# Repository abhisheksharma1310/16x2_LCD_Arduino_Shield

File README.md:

# 16x2_LCD_Arduino_Shield
This is a PCB Design for an Arduino shield that can be stacked on top of the Arduino Board. It contains a 16x2 LCD Display which is used to display Sensor data or desired message on the 16x2 LCD Display. It also has one NRF24 Wireless Transmitter to send data wirelessly to display on 16x2 LCD.

Top view

Bottom view

Schematic

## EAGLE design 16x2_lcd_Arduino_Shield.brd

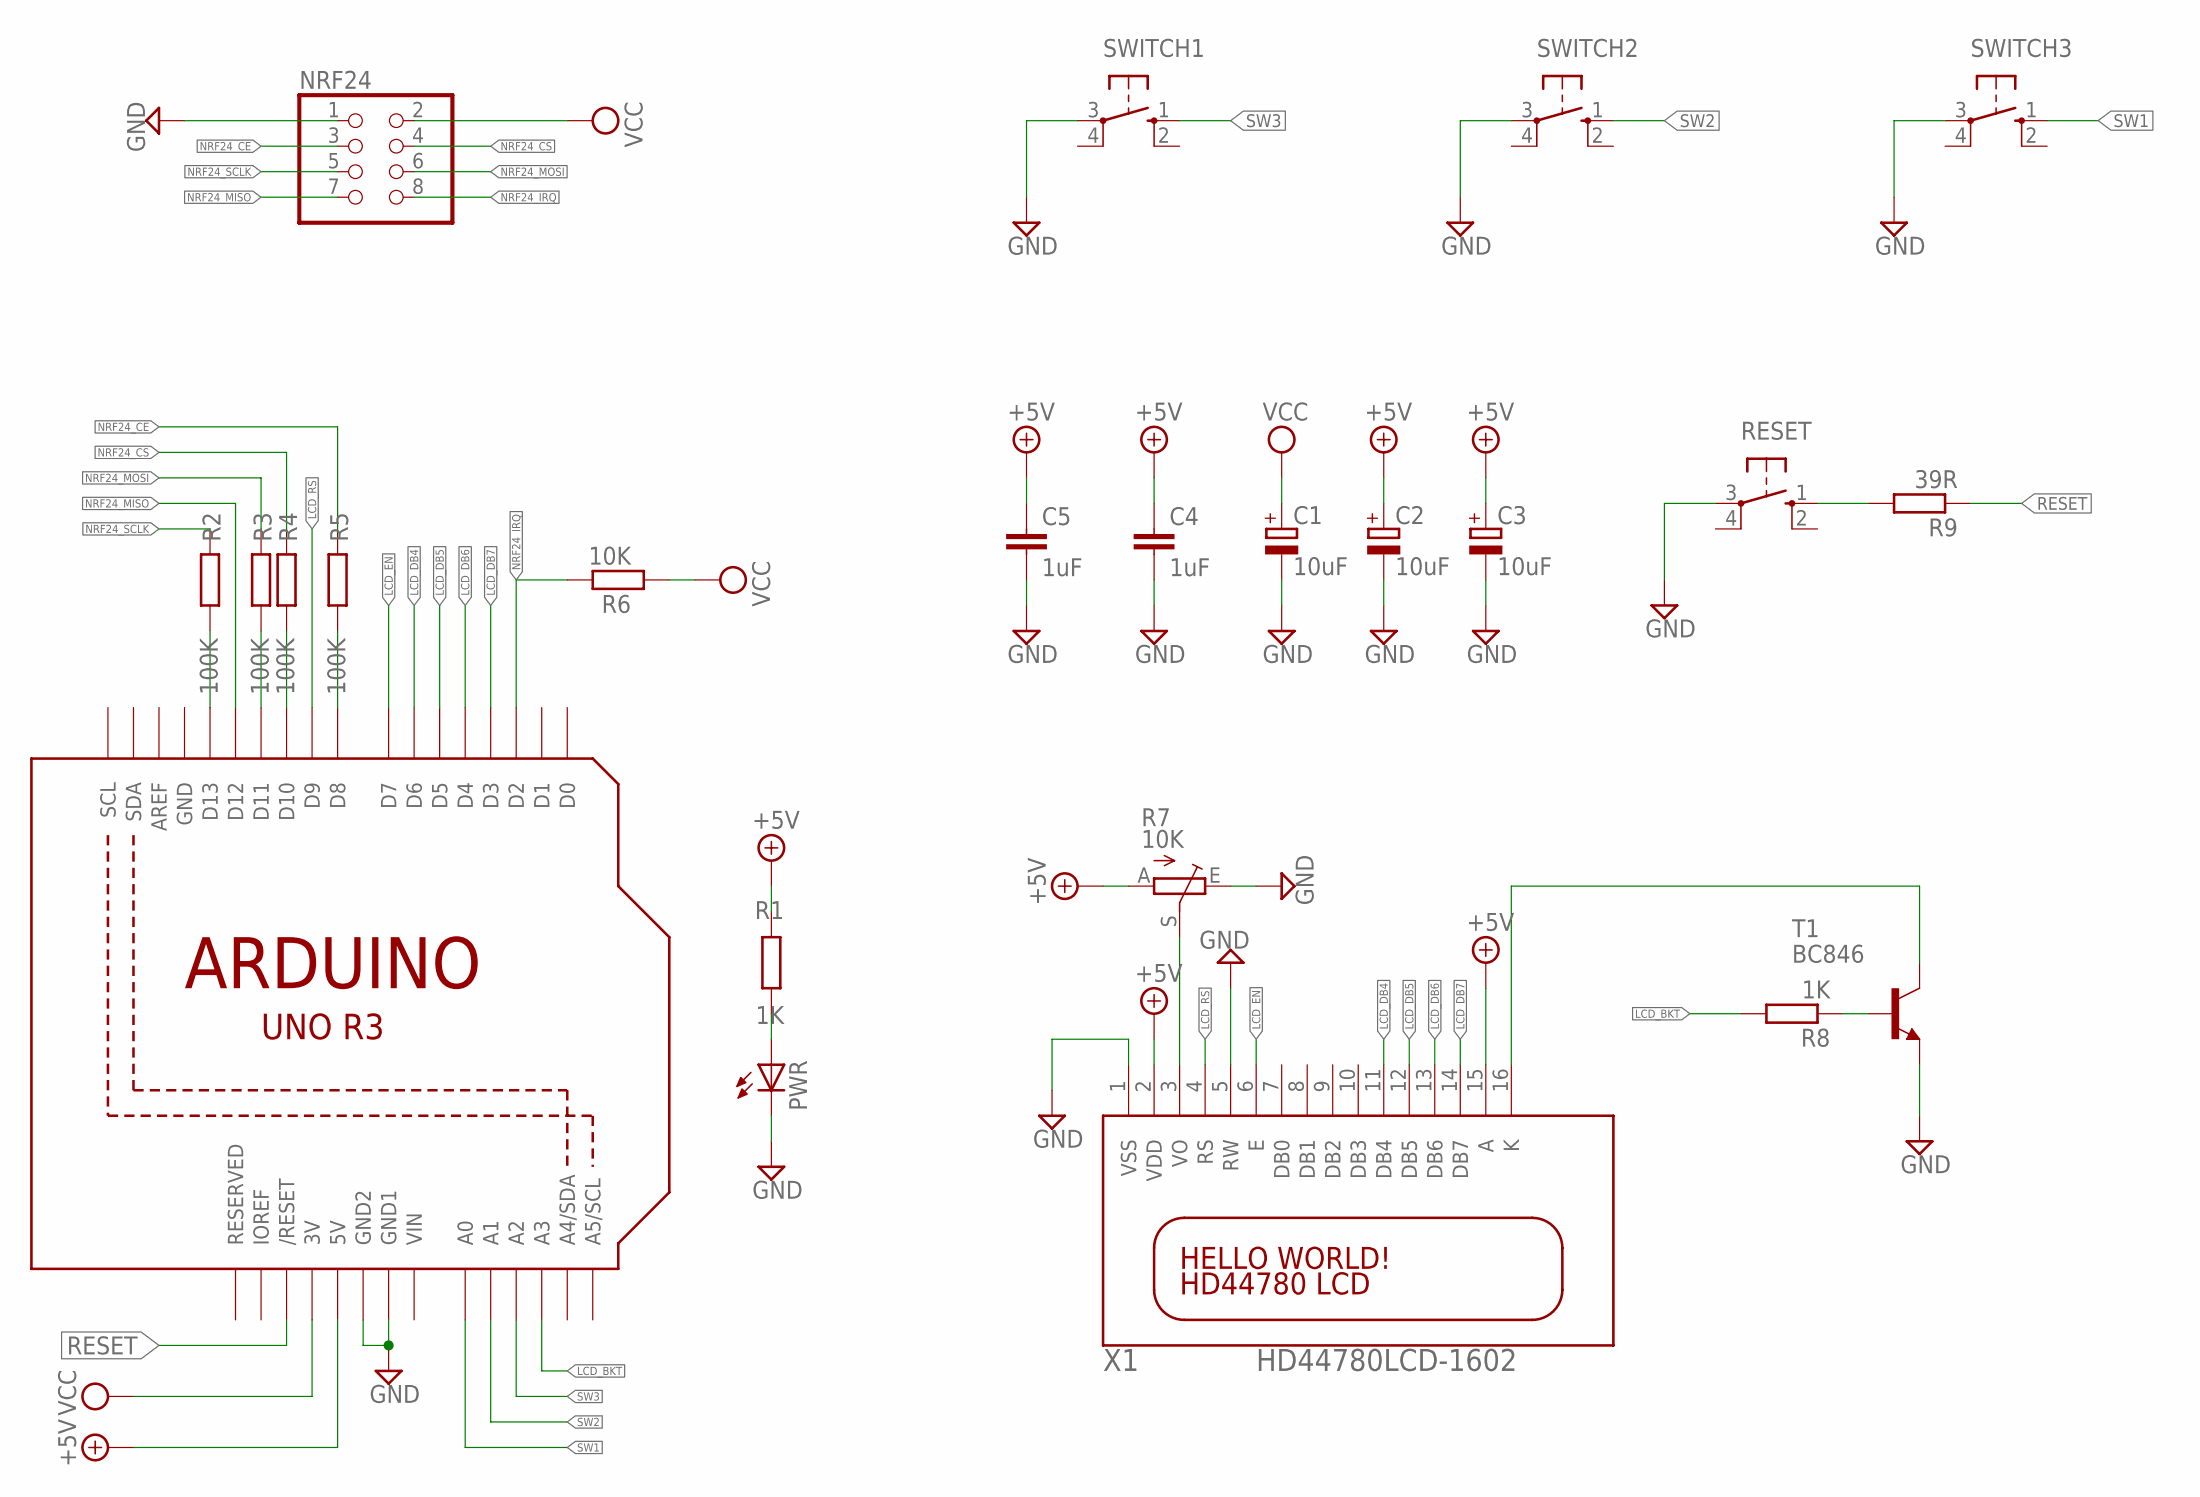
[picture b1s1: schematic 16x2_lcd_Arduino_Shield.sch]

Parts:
C1, C2, C3: 10uF; CT3216
C4, C5: 1uF; C1206
NRF24: PINHD-2X4; 2X04
PWR: LED5MM
R1, R8: 1K; R1206
R2, R3, R4, R5: 100K; R1206
R6: 10K; R1206
R7: 10K; RJ9W
R9: 39R; R1206
RESET: 10-XX; B3F-10XX
SWITCH1, SWITCH2, SWITCH3: 10-XX; B3F-10XX
T1: BC846; SOT23
U1: ARDUINOR3-BPLACE
X1: HD44780LCD-1602; LCD1602

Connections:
+5V: C2.+, C3.+, C4.1, C5.1, R1.2, R7.A, U1.5V, X1.2 (VDD), X1.15 (A)
GND: C1.-, C2.-, C3.-, C4.2, C5.2, NRF24.1, PWR.K (C), R7.E, RESET.3, SWITCH1.3, SWITCH2.3, SWITCH3.3, T1.2 (E), U1.GND, U1.GND1, U1.GND2, X1.1 (VSS), X1.5 (RW)
LCD_BKT: R8.2, U1.A3
LCD_DB4: U1.D6, X1.11 (DB4)
LCD_DB5: U1.D5, X1.12 (DB5)
LCD_DB6: U1.D4, X1.13 (DB6)
LCD_DB7: U1.D3, X1.14 (DB7)
LCD_EN: U1.D7, X1.6 (E)
LCD_RS: U1.D9, X1.4 (RS)
unnamed: PWR.A, R1.1
unnamed: R2.1, U1.D13
unnamed: R7.S, X1.3 (VO)
unnamed: R3.1, U1.D11
unnamed: R4.1, U1.D10
unnamed: T1.3 (C), X1.16 (K)
unnamed: R5.1, U1.D8
unnamed: R8.1, T1.1 (B)
unnamed: R9.2, RESET.1 (S)
NRF24_CE: NRF24.3, R5.2
NRF24_CS: NRF24.4, R4.2
NRF24_IRQ: NRF24.8, R6.2, U1.D2
NRF24_MISO: NRF24.7, U1.D12
NRF24_MOSI: NRF24.6, R3.2
NRF24_SCLK: NRF24.5, R2.2
RESET: R9.1, U1.RESET (/RESET)
SW1: SWITCH3.1 (S), U1.A0
SW2: SWITCH2.1 (S), U1.A1
SW3: SWITCH1.1 (S), U1.A2
VCC: C1.+, NRF24.2, R6.1, U1.3V
VIN: U1.VIN

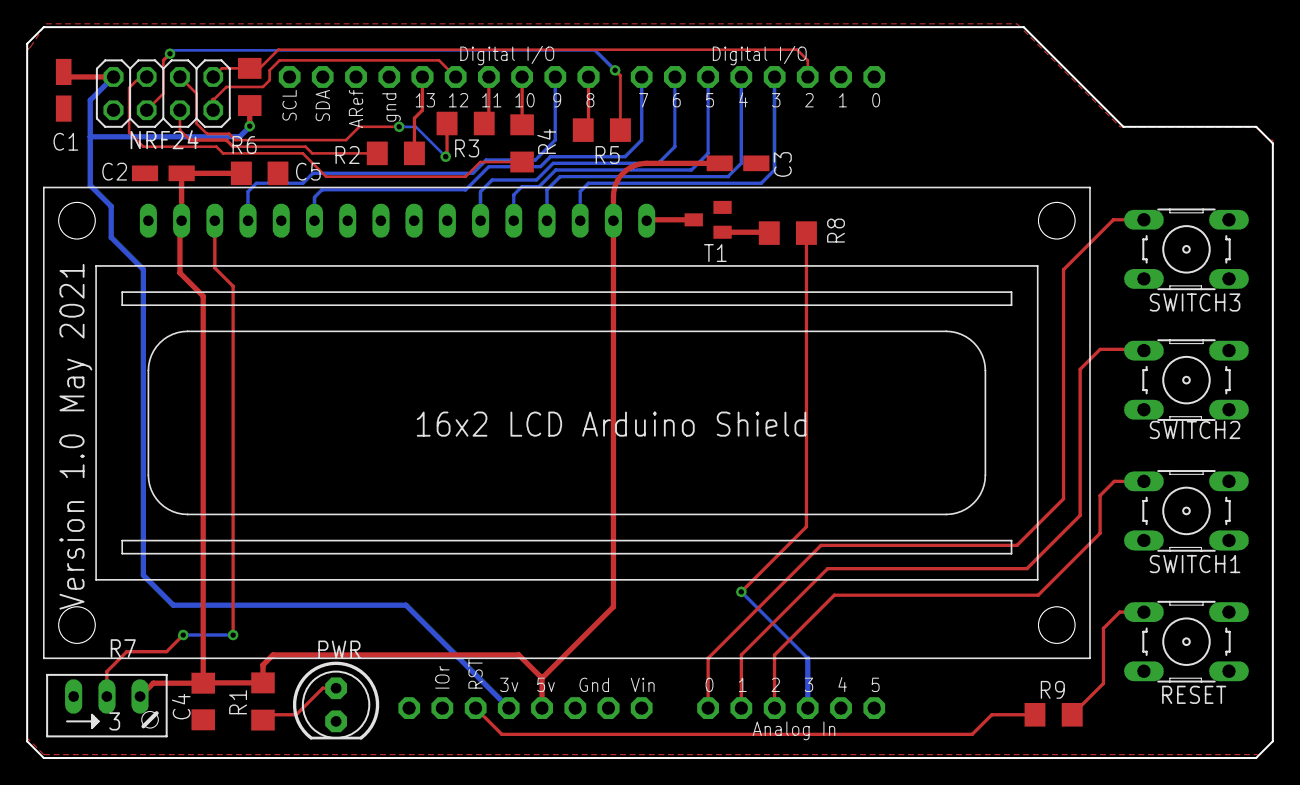
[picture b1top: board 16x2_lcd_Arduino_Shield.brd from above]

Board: 2 copper layers, 95.2 x 55.9 mm, 23 parts (0 on the bottom side), 29 nets.
